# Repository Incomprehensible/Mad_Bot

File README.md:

# Mad_Bot
Exploratory project in Embedded Robotics and Swarm Algorithms

Warning: This is an ongoing project, and the repository is under construction!

## Features
* Small PCB-based frame, minimum 3D printed parts
* ESP32-S3 MCU with vector instructions, acceleration for neural network computing and signal processing workloads
* Wi-Fi, Bluetooth 5 and BLE connectivity
* Omnidirectional movement
* Quadrature encoders for precise movement
* 8 MB PSRAM for image processing
* 2 Megapixel camera and ToF sensors for running embedded robotics algorithms
* Powered via USB-C or 3000mAh LiPo battery with inner protection and external charging circuit
* Load sharing circuit for operating the robot while charging
* Buck-Boost converter for powering the MCU and peripherals
* 6V regulator for powering the middle power range motors
* ESPNOW, ESP-WIFI-MESH or ESP-BLE-MESH for communication between several robots
* Integrated MEMS microphone for sound recognition
* micro-ROS support

**Note**: Software support for some features is still in progress.

## Fusion360 design
| | |
|--------------|------------|
|  |  |
|  |  |

## URDF model
<details>

| Robot | Wheel |
|--------------|------------|
|  |  |

</details>

## Operation demo
<details>

| Forward movement | Backward movement | Rotation |
|:----------------:|:-----------------:|:--------:|
|  |  |  |
<!-- |  |  |  | -->

</details>

### Charging mode
<details>

</details>

## Board layout
<details>

</details>

## Future work
- [ ] Add a BOM
- [X] Design a carrier extension in Fusion360
- [X] Test battery charging circuit
- [X] Test load sharing circuit
- [X] Test basic functionality with motors and ESP32-S3
- [X] Test Wi-Fi
- [X] Motors library (in progress)
- [X] Encoders testing
- [ ] **Device firmware (in progress)**
- [ ] **Sensors testing (in progress)**:
  - [ ] Camera
  - [X] ToF
  - [X] IMU
  - [ ] *MEMS microphone (requires PCB bug fix)*
- [ ] Remote controller based on ESP32
- [ ] PSRAM memory testing
- [X] **ROS2 integration via micro-ROS (in progress)**
- [ ] Web page with control interface and telemetry
- [X] URDF model
- [X] Joystick control via ROS2
- [ ] Digital twin for simulation in Gazebo and Mujoco
- [ ] ESPNOW and Mesh experiments
- [ ] Multi-agent algorithms
- [ ] Computer vision algorithms
- [ ] Mini SLAM experiments

## Fix list for new hardware revisions
* MEMS microphone footprint flipped
* Non-fixed Buck-Boost mentioned in the schematics instead of 3.3V fixed
* 6V regulator doesn't disconnect the load if disabled because of topology - extra switch needed
* Battery connector is hard to remove - source power switch needed
* Better (aligned) placement for camera & ToF sensors

## Software Troubleshooting

### micro-ROS build issues
If you encounter issue like [this](https://github.com/micro-ROS/micro_ros_espidf_component/issues/251) building micro-ROS for the ESP32-S3 platform, edit [`libmicroros.mk`](https://github.com/micro-ROS/micro_ros_espidf_component/blob/humble/libmicroros.mk) file at line 110 to include `esp32s3` as follows:

```makefile
ifeq ($(IDF_TARGET),$(filter $(IDF_TARGET),esp32s2 esp32c3 esp32c6 esp32s3))
```

## Acknowledgements
This project takes inspiration from the following open-source projects:
* https://github.com/YePeOn7/ros2_omni_robot_sim (omnidirectional drive kinematics)
* https://github.com/twistx77/V53L7CX-Library.git (ToF sensor library)
* https://github.com/natanaeljr/esp32-mpu-driver (IMU driver)
* Jonas Scharpf code pf the PCA9685 driver (motor PWM driver)

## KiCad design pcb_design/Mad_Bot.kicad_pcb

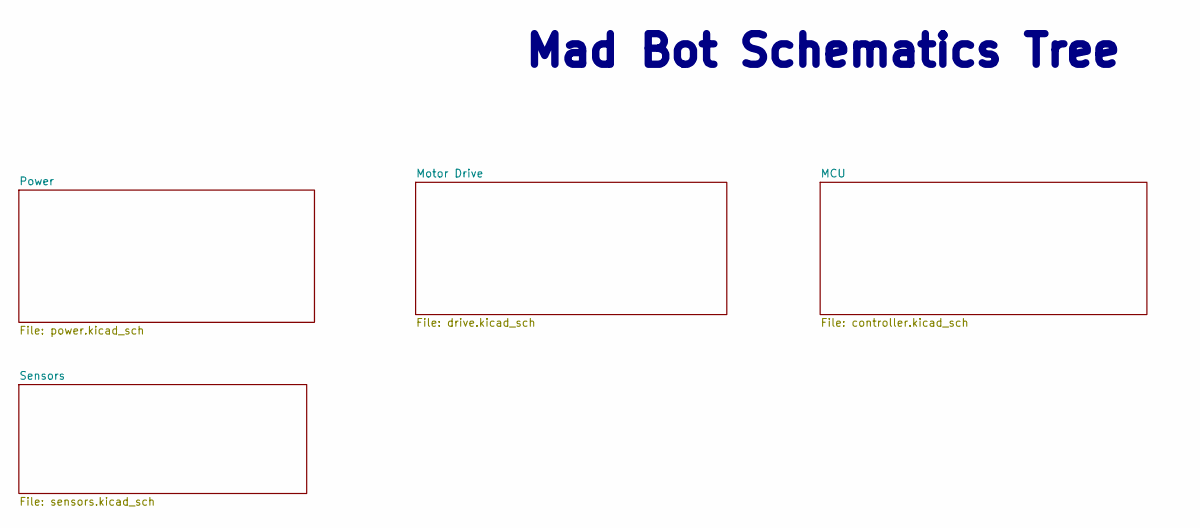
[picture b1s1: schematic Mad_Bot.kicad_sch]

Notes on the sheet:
Mad Bot Schematics Tree

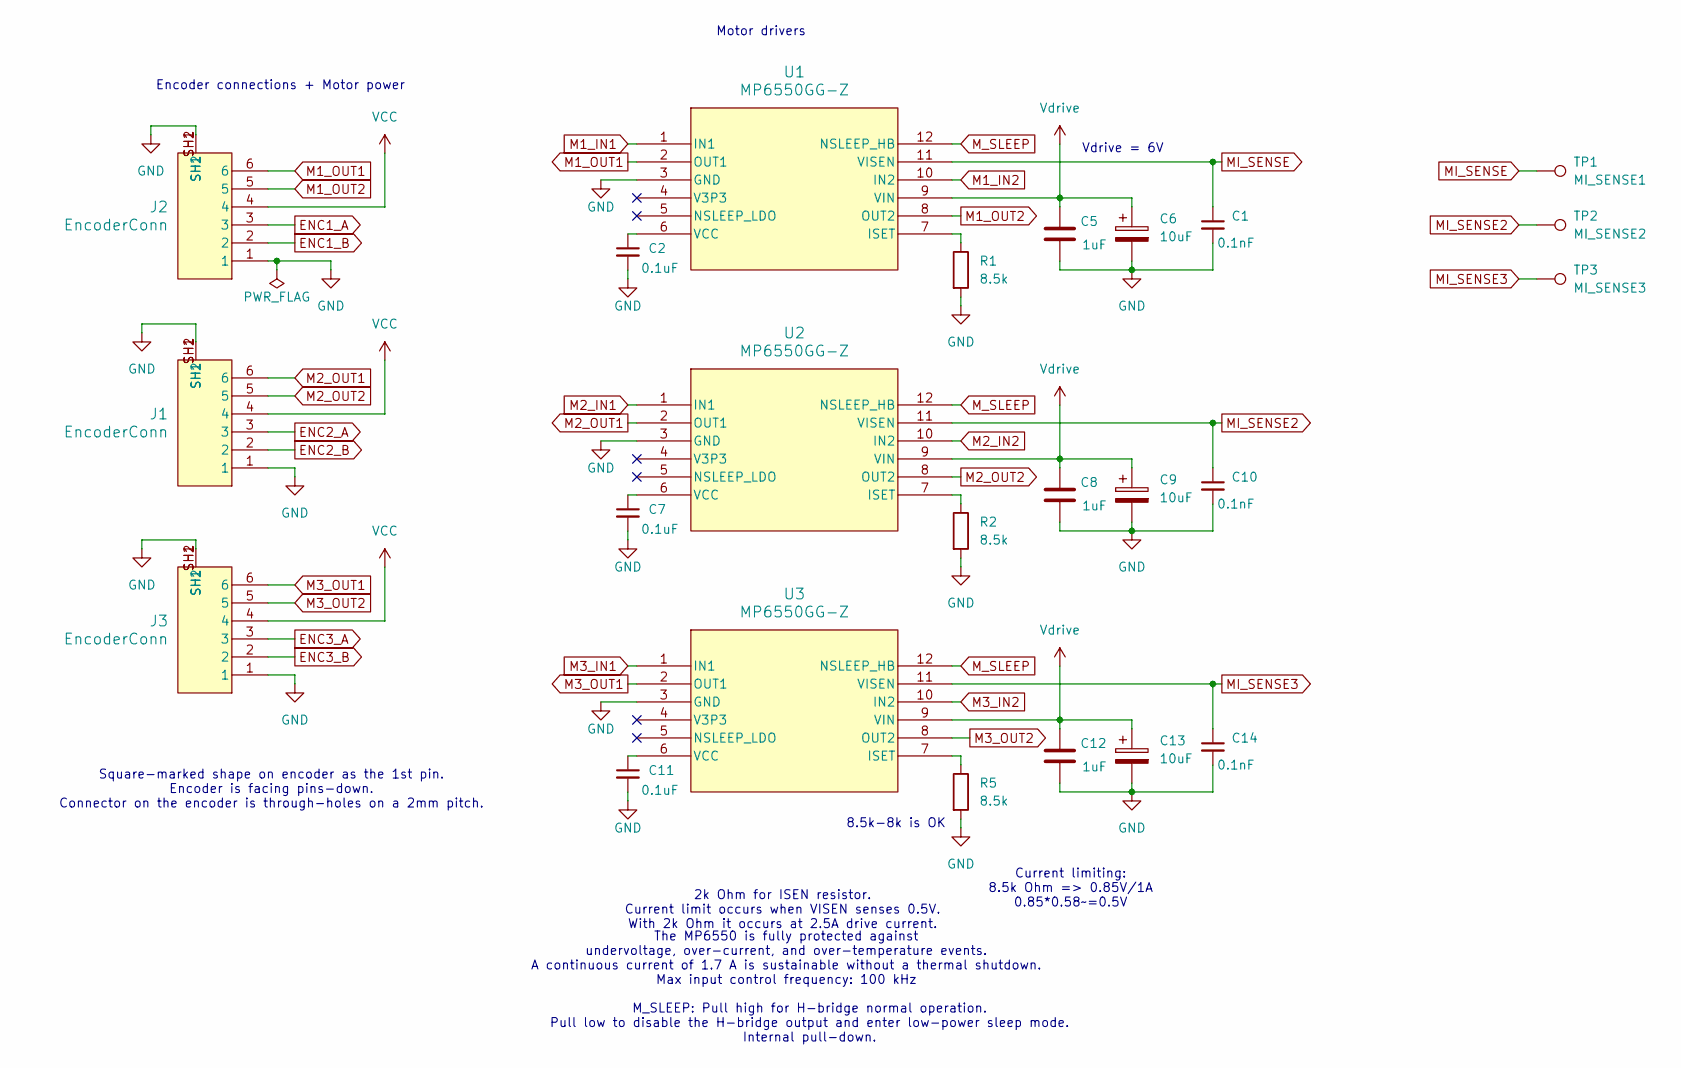
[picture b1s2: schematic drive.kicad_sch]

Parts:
C1, C10, C14: 0.1nF; C_0402_1005Metric_Pad0.74x0.62mm_HandSolder
C2, C7, C11: 0.1uF; C_0603_1608Metric_Pad1.08x0.95mm_HandSolder
C5, C8, C12: 1uF; CP_EIA-3216-18_Kemet-A_Pad1.58x1.35mm_HandSolder
C6, C9, C13: 10uF; C_1206_3216Metric_Pad1.33x1.80mm_HandSolder
J1, J2, J3: EncoderConn; JST_S6B-ZR-SM4A-TF_1.5mm
R1, R2, R5: 8.5k; R_0603_1608Metric_Pad0.98x0.95mm_HandSolder
TP1: MI_SENSE1; TestPoint_Pad_1.5x1.5mm
TP2: MI_SENSE2; TestPoint_Pad_1.5x1.5mm
TP3: MI_SENSE3; TestPoint_Pad_1.5x1.5mm
U1, U2, U3: MP6550GG-Z; IC12_MP6550_MNP

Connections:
ENC1_A: J2.3; also elsewhere on the board
ENC1_B: J2.2; also elsewhere on the board
ENC2_A: J1.3; also elsewhere on the board
ENC2_B: J1.2; also elsewhere on the board
ENC3_A: J3.3; also elsewhere on the board
ENC3_B: J3.2; also elsewhere on the board
GND: C1.2, C2.2, C5.2, C6.2, C7.2, C8.2, C9.2, C10.2, C11.2, C12.2, C13.2, C14.2, J1.1, J1.SH1, J1.SH2, J2.1, J2.SH1, J2.SH2, J3.1, J3.SH1, J3.SH2, R1.2, R2.2, R5.2, U1.3 (GND), U2.3 (GND), U3.3 (GND); also elsewhere on the board
M1_IN1: U1.1 (IN1); also elsewhere on the board
M1_IN2: U1.10 (IN2); also elsewhere on the board
M1_OUT1: J2.6, U1.2 (OUT1)
M1_OUT2: J2.5, U1.8 (OUT2)
M2_IN1: U2.1 (IN1); also elsewhere on the board
M2_IN2: U2.10 (IN2); also elsewhere on the board
M2_OUT1: J1.6, U2.2 (OUT1)
M2_OUT2: J1.5, U2.8 (OUT2)
M3_IN1: U3.1 (IN1); also elsewhere on the board
M3_IN2: U3.10 (IN2); also elsewhere on the board
M3_OUT1: J3.6, U3.2 (OUT1)
M3_OUT2: J3.5, U3.8 (OUT2)
MI_SENSE: C1.1, TP1.1, U1.11 (VISEN)
MI_SENSE2: C10.1, TP2.1, U2.11 (VISEN)
MI_SENSE3: C14.1, TP3.1, U3.11 (VISEN)
M_SLEEP: U1.12 (NSLEEP_HB), U2.12 (NSLEEP_HB), U3.12 (NSLEEP_HB); also elsewhere on the board
unnamed: R1.1, U1.7 (ISET)
unnamed: C2.1, U1.6 (VCC)
unnamed: R2.1, U2.7 (ISET)
unnamed: C7.1, U2.6 (VCC)
unnamed: R5.1, U3.7 (ISET)
unnamed: C11.1, U3.6 (VCC)
VCC: J1.4, J2.4, J3.4; also elsewhere on the board
Vdrive: C5.1, C6.1, C8.1, C9.1, C12.1, C13.1, U1.9 (VIN), U2.9 (VIN), U3.9 (VIN); also elsewhere on the board

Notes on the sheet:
M_SLEEP: Pull high for H-bridge normal operation. Pull low to disable the H-bridge output and enter low-power sleep mode. Internal pull-down.
Square-marked shape on encoder as the 1st pin. Encoder is facing pins-down. Connector on the encoder is through-holes on a 2mm pitch.
Motor drivers
8.5k-8k is OK
Current limiting: 8.5k Ohm => 0.85V/1A 0.85*0.58~=0.5V
Vdrive = 6V
Encoder connections + Motor power
The MP6550 is fully protected against undervoltage, over-current, and over-temperature events. A continuous current of 1.7 A is sustainable without a thermal shutdown. Max input control frequency: 100 kHz
2k Ohm for ISEN resistor. Current limit occurs when VISEN senses 0.5V. With 2k Ohm it occurs at 2.5A drive current.

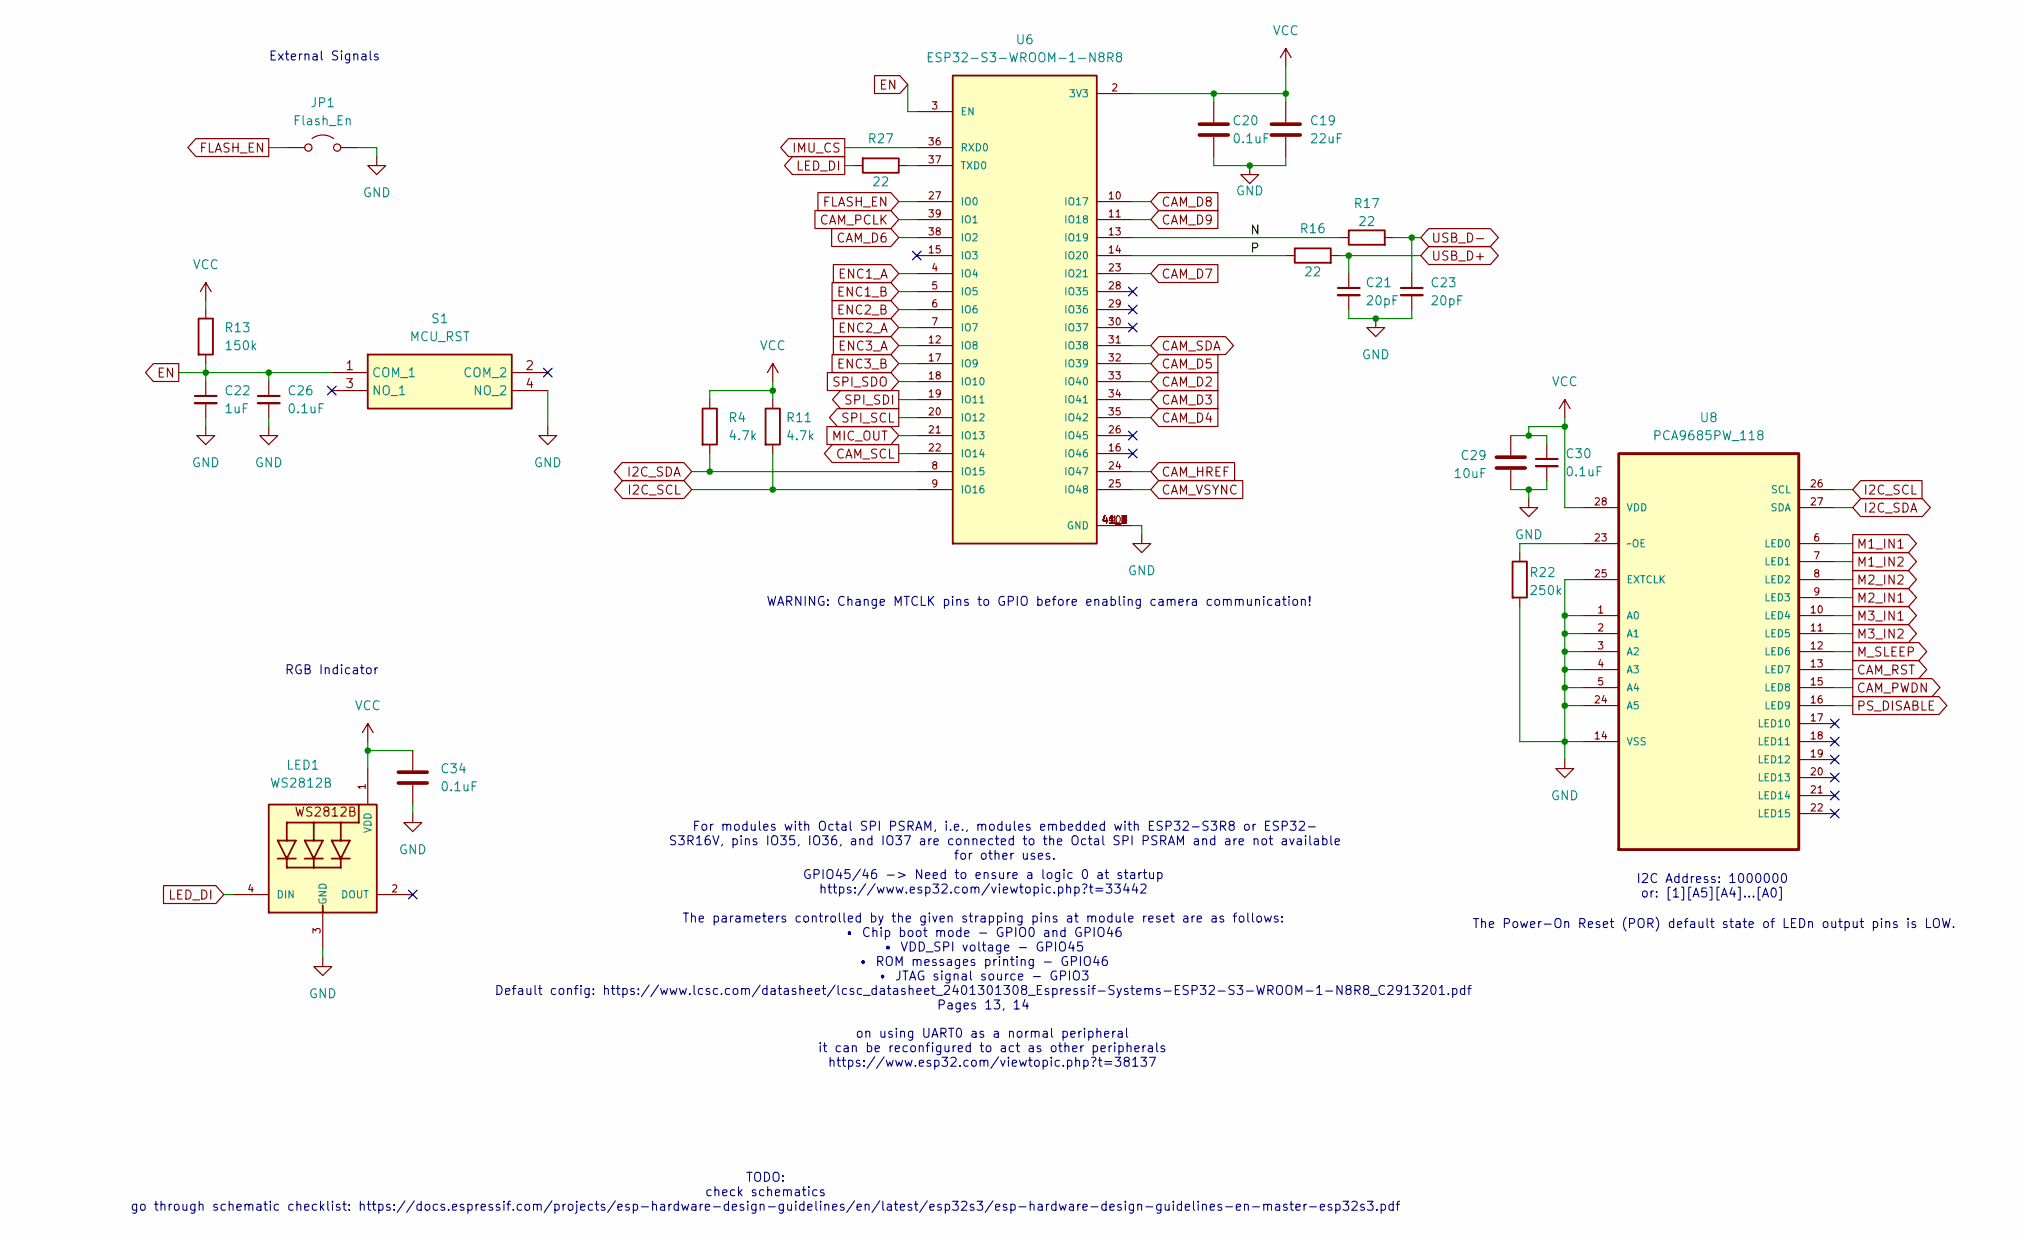
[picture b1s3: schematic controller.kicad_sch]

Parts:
C19: 22uF; C_0603_1608Metric_Pad1.08x0.95mm_HandSolder
C20, C26, C30, C34: 0.1uF; C_0603_1608Metric_Pad1.08x0.95mm_HandSolder
C21, C23: 20pF; C_0402_1005Metric_Pad0.74x0.62mm_HandSolder
C22: 1uF; CP_EIA-3216-18_Kemet-A_Pad1.58x1.35mm_HandSolder
C29: 10uF; C_1206_3216Metric_Pad1.33x1.80mm_HandSolder
JP1: Flash_En; Flash_Jumper_1x02_P2.00mm_Vertical
LED1: WS2812B
R4, R11: 4.7k; R_0603_1608Metric_Pad0.98x0.95mm_HandSolder
R13: 150k; R_0603_1608Metric_Pad0.98x0.95mm_HandSolder
R16, R17: 22; R_0402_1005Metric_Pad0.72x0.64mm_HandSolder
R22: 250k; R_0603_1608Metric_Pad0.98x0.95mm_HandSolder
R27: 22; R_0603_1608Metric_Pad0.98x0.95mm_HandSolder
S1: MCU_RST; PTS526SK15SMTR2LFS; Manufacturer_Part_Number PTS526 SK15 SMTR2 LFS; Mouser Part Number 611-PTS526SK15SMR2L
U6: ESP32-S3-WROOM-1-N8R8; XCVR_ESP32S3WROOM1N8R8
U8: PCA9685PW_118; SOP65P640X110-28N; MPN PCA9685PW,118

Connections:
/MCU/N: R17.1, U6.13 (IO19)
/MCU/P: R16.1, U6.14 (IO20)
CAM_D2: U6.33 (IO40); also elsewhere on the board
CAM_D3: U6.34 (IO41); also elsewhere on the board
CAM_D4: U6.35 (IO42); also elsewhere on the board
CAM_D5: U6.32 (IO39); also elsewhere on the board
CAM_D6: U6.38 (IO2); also elsewhere on the board
CAM_D7: U6.23 (IO21); also elsewhere on the board
CAM_D8: U6.10 (IO17); also elsewhere on the board
CAM_D9: U6.11 (IO18); also elsewhere on the board
CAM_HREF: U6.24 (IO47); also elsewhere on the board
CAM_PCLK: U6.39 (IO1); also elsewhere on the board
CAM_PWDN: U8.15 (LED8); also elsewhere on the board
CAM_RST: U8.13 (LED7); also elsewhere on the board
CAM_SCL: U6.22 (IO14); also elsewhere on the board
CAM_SDA: U6.31 (IO38); also elsewhere on the board
CAM_VSYNC: U6.25 (IO48); also elsewhere on the board
EN: C22.1, C26.1, R13.2, S1.1 (COM_1), U6.3 (EN)
ENC1_A: U6.4 (IO4); also elsewhere on the board
ENC1_B: U6.5 (IO5); also elsewhere on the board
ENC2_A: U6.7 (IO7); also elsewhere on the board
ENC2_B: U6.6 (IO6); also elsewhere on the board
ENC3_A: U6.12 (IO8); also elsewhere on the board
ENC3_B: U6.17 (IO9); also elsewhere on the board
FLASH_EN: JP1.1 (A), U6.27 (IO0)
GND: C19.2, C20.2, C21.2, C22.2, C23.2, C26.2, C29.1, C30.2, C34.2, JP1.2 (B), LED1.3 (GND), R22.2, S1.4 (NO_2), U6.1 (GND), U6.40 (GND), U6.41_1 (GND), U6.41_2 (GND), U6.41_3 (GND), U6.41_4 (GND), U6.41_5 (GND), U6.41_6 (GND), U6.41_7 (GND), U6.41_8 (GND), U6.41_9 (GND), U8.1 (A0), U8.2 (A1), U8.3 (A2), U8.4 (A3), U8.5 (A4), U8.14 (VSS), U8.24 (A5), U8.25 (EXTCLK); also elsewhere on the board
I2C_SCL: R11.2, U6.9 (IO16), U8.26 (SCL); also elsewhere on the board
I2C_SDA: R4.2, U6.8 (IO15), U8.27 (SDA); also elsewhere on the board
IMU_CS: U6.36 (RXD0); also elsewhere on the board
LED_DI: LED1.4 (DIN), R27.2
M1_IN1: U8.6 (LED0); also elsewhere on the board
M1_IN2: U8.7 (LED1); also elsewhere on the board
M2_IN1: U8.9 (LED3); also elsewhere on the board
M2_IN2: U8.8 (LED2); also elsewhere on the board
M3_IN1: U8.10 (LED4); also elsewhere on the board
M3_IN2: U8.11 (LED5); also elsewhere on the board
MIC_OUT: U6.21 (IO13); also elsewhere on the board
M_SLEEP: U8.12 (LED6); also elsewhere on the board
unnamed: R27.1, U6.37 (TXD0)
unnamed: R22.1, U8.23 (~OE)
PS_DISABLE: U8.16 (LED9); also elsewhere on the board
SPI_SCL: U6.20 (IO12); also elsewhere on the board
SPI_SDI: U6.19 (IO11); also elsewhere on the board
SPI_SDO: U6.18 (IO10); also elsewhere on the board
USB_D+: C21.1, R16.2; also elsewhere on the board
USB_D-: C23.1, R17.2; also elsewhere on the board
VCC: C19.1, C20.1, C29.2, C30.1, C34.1, LED1.1 (VDD), R4.1, R11.1, R13.1, U6.2 (3V3), U8.28 (VDD); also elsewhere on the board

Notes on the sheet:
GPIO45/46 -> Need to ensure a logic 0 at startup https://www.esp32.com/viewtopic.php?t=33442 The parameters controlled by the given strapping pins at module reset are as follows: • Chip boot mode - GPIO0 and GPIO46 • VDD_SPI voltage - GPIO45 • ROM messages printing - GPIO46 • JTAG signal source - G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
TODO: check schematics go through schematic checklist: https://docs.espressif.com/projects/esp-hardware-design-guidelines/en/latest/esp32s3/esp-hardware-design-guidelines-en-master-esp32s3.pdf
External Signals
I2C Address: 1000000 or: [1][A5][A4]...[A0]
on using UART0 as a normal peripheral it can be reconfigured to act as other peripherals https://www.esp32.com/viewtopic.php?t=38137
The Power-On Reset (POR) default state of LEDn output pins is LOW.
RGB Indicator
For modules with Octal SPI PSRAM, i.e., modules embedded with ESP32-S3R8 or ESP32- S3R16V, pins IO35, IO36, and IO37 are connected to the Octal SPI PSRAM and are not available for other uses.
WARNING: Change MTCLK pins to GPIO before enabling camera communication!

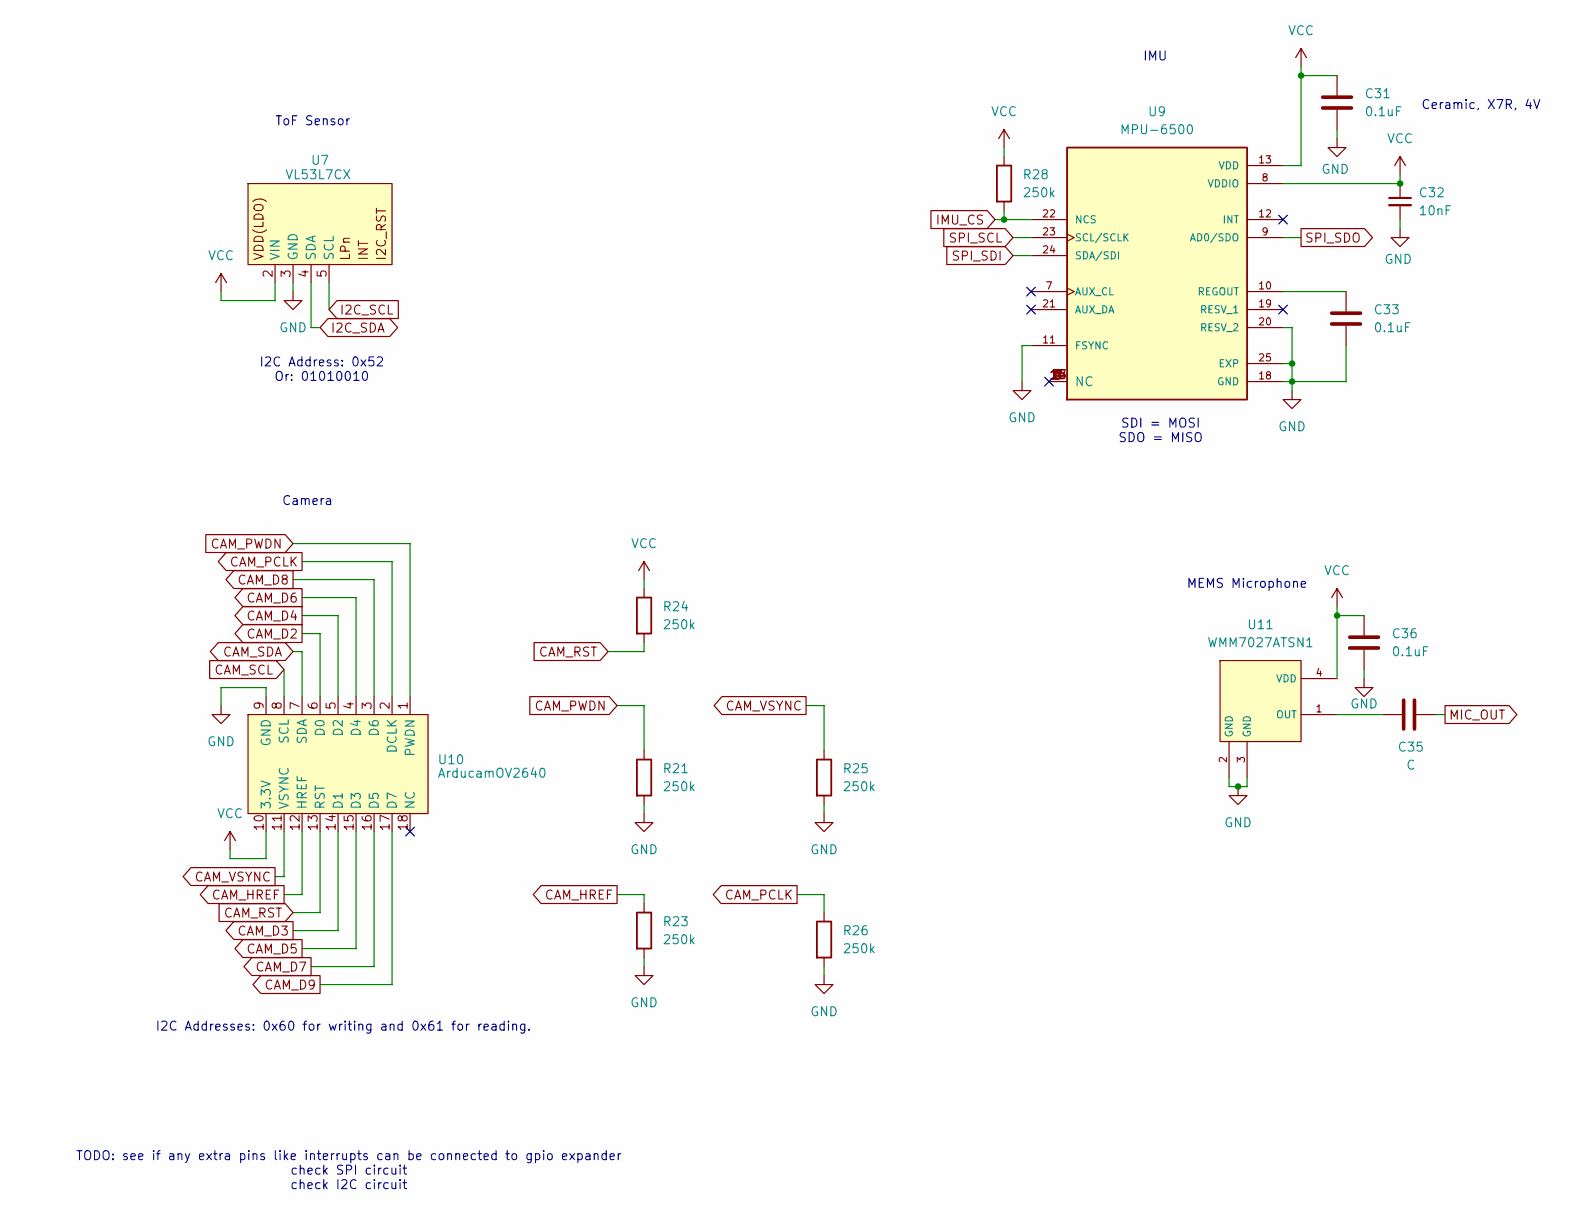
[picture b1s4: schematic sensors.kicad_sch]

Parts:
C31, C33, C36: 0.1uF; C_0603_1608Metric_Pad1.08x0.95mm_HandSolder
C32: 10nF; C_0603_1608Metric_Pad1.08x0.95mm_HandSolder
C35: C; C_0603_1608Metric_Pad1.08x0.95mm_HandSolder
R21, R23, R24, R25, R26, R28: 250k; R_0603_1608Metric_Pad0.98x0.95mm_HandSolder
U7: VL53L7CX; CONN_S4B-XH-SM4-TB_JST
U9: MPU-6500; QFN24_3X3X0P9_MPU6500; PARTREV 1.3
U10: ArducamOV2640; Arducam_Socket_2x09_P2.54mm_Vertical_SMD
U11: WMM7027ATSN1; WMM7027ATSN1-4TR

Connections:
CAM_D2: U10.6 (D0); also elsewhere on the board
CAM_D3: U10.14 (D1); also elsewhere on the board
CAM_D4: U10.5 (D2); also elsewhere on the board
CAM_D5: U10.15 (D3); also elsewhere on the board
CAM_D6: U10.4 (D4); also elsewhere on the board
CAM_D7: U10.16 (D5); also elsewhere on the board
CAM_D8: U10.3 (D6); also elsewhere on the board
CAM_D9: U10.17 (D7); also elsewhere on the board
CAM_HREF: R23.1, U10.12 (HREF); also elsewhere on the board
CAM_PCLK: R26.1, U10.2 (DCLK); also elsewhere on the board
CAM_PWDN: R21.1, U10.1 (PWDN); also elsewhere on the board
CAM_RST: R24.2, U10.13 (RST); also elsewhere on the board
CAM_SCL: U10.8 (SCL); also elsewhere on the board
CAM_SDA: U10.7 (SDA); also elsewhere on the board
CAM_VSYNC: R25.1, U10.11 (VSYNC); also elsewhere on the board
GND: C31.2, C32.2, C33.2, C36.2, R21.2, R23.2, R25.2, R26.2, U7.3 (GND), U9.11 (FSYNC), U9.18 (GND), U9.20 (RESV_2), U9.25 (EXP), U10.9 (GND), U11.2 (GND), U11.3 (GND); also elsewhere on the board
I2C_SCL: U7.5 (SCL); also elsewhere on the board
I2C_SDA: U7.4 (SDA); also elsewhere on the board
IMU_CS: R28.2, U9.22 (NCS); also elsewhere on the board
MIC_OUT: C35.2; also elsewhere on the board
unnamed: C33.1, U9.10 (REGOUT)
unnamed: C35.1, U11.1 (OUT)
SPI_SCL: U9.23 (SCL/SCLK); also elsewhere on the board
SPI_SDI: U9.24 (SDA/SDI); also elsewhere on the board
SPI_SDO: U9.9 (AD0/SDO); also elsewhere on the board
VCC: C31.1, C32.1, C36.1, R24.1, R28.1, U7.2 (VIN), U9.8 (VDDIO), U9.13 (VDD), U10.10 (3.3V), U11.4 (VDD); also elsewhere on the board

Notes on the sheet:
SDI = MOSI SDO = MISO
Camera
I2C Addresses: 0x60 for writing and 0x61 for reading.
TODO: see if any extra pins like interrupts can be connected to gpio expander check SPI circuit check I2C circuit
Ceramic, X7R, 4V
ToF Sensor
I2C Address: 0x52 Or: 01010010
IMU
MEMS Microphone

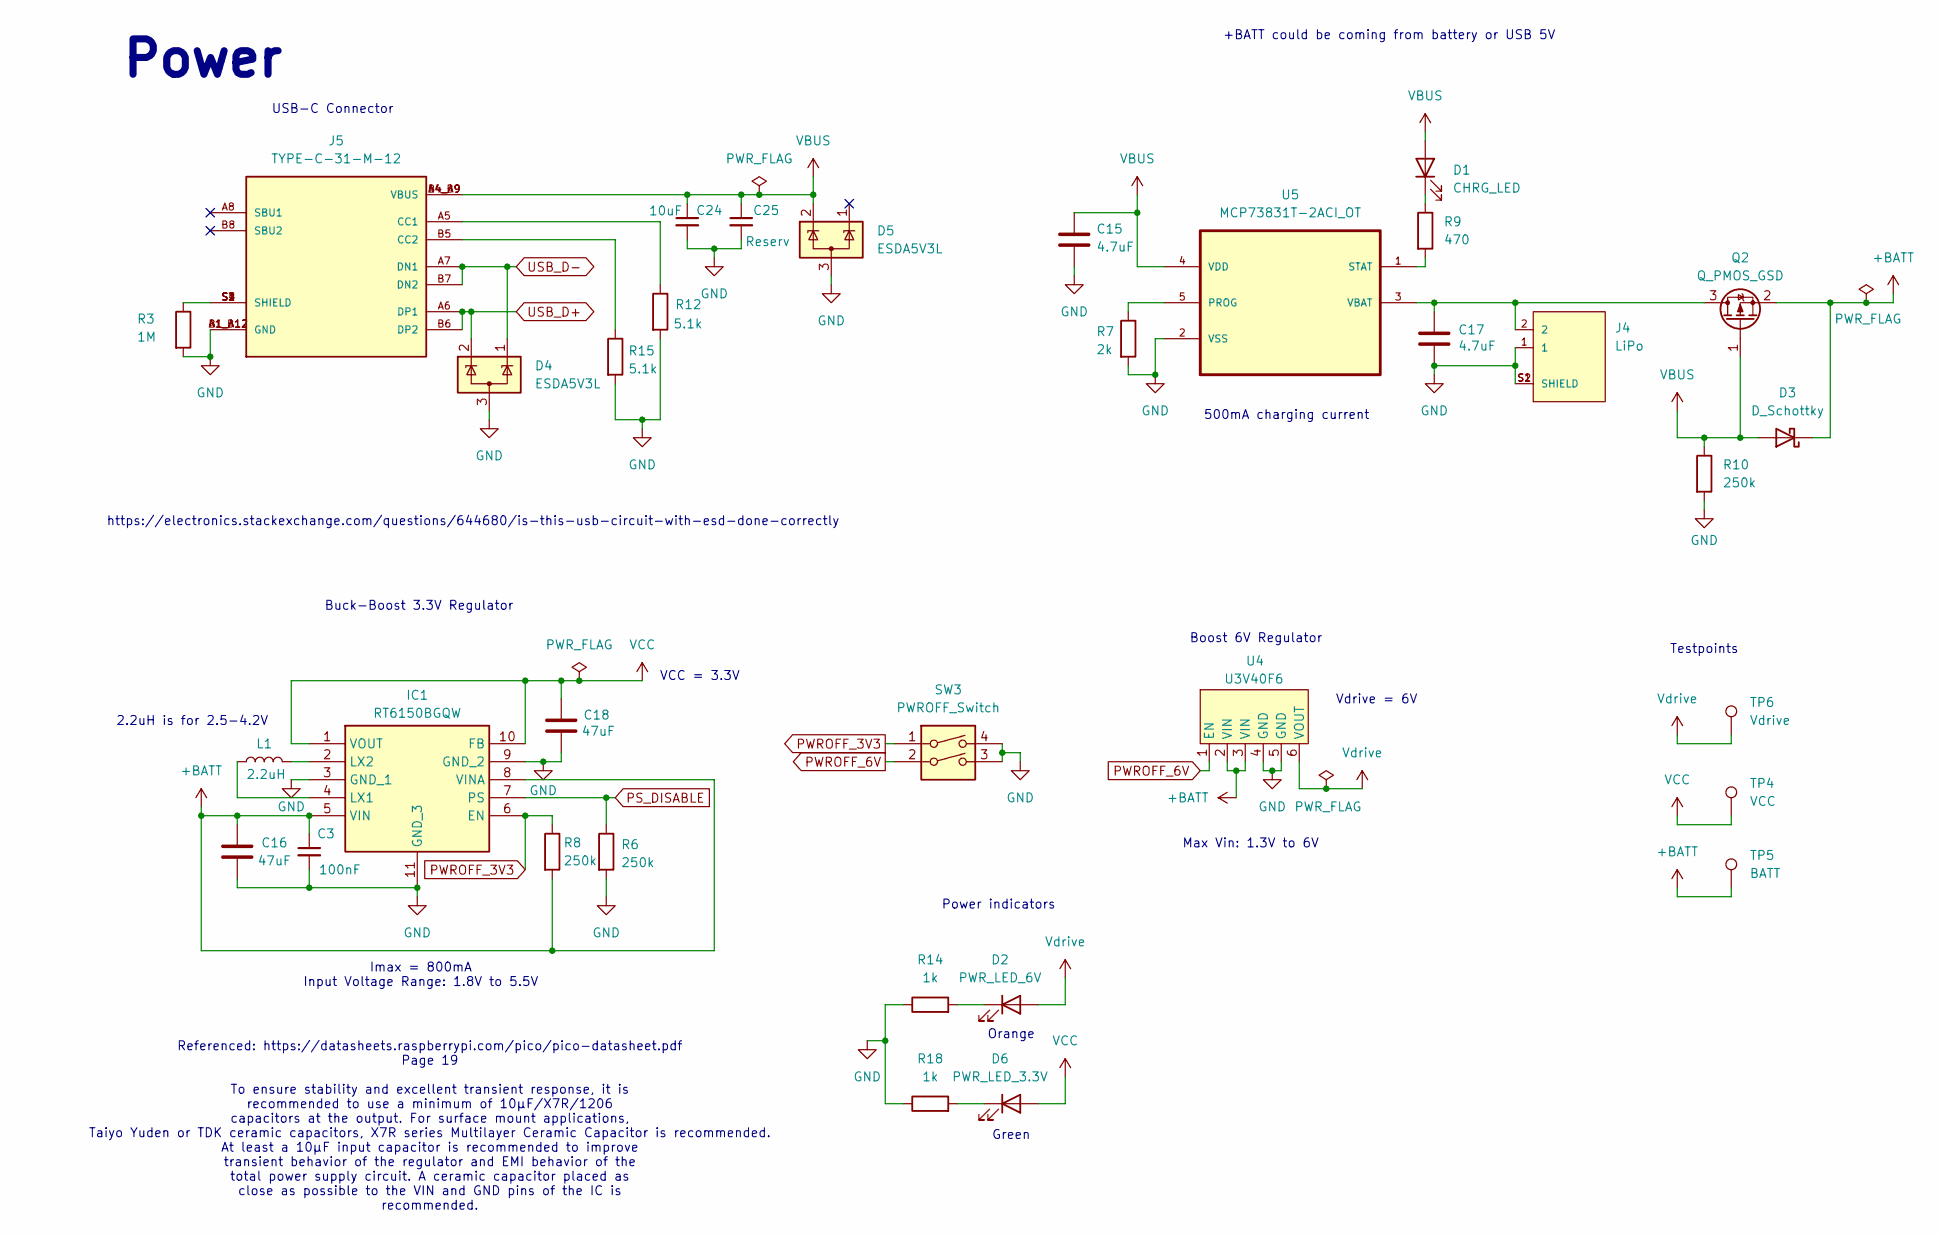
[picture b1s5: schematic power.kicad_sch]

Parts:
C3: 100nF; C_0603_1608Metric_Pad1.08x0.95mm_HandSolder
C15, C17: 4.7uF; C_0603_1608Metric_Pad1.08x0.95mm_HandSolder
C16, C18: 47uF; C_1210_3225Metric_Pad1.33x2.70mm_HandSolder
C24: 10uF; C_1206_3216Metric_Pad1.33x1.80mm_HandSolder
C25: Reserv; C_0603_1608Metric_Pad1.08x0.95mm_HandSolder
D1: CHRG_LED; LED_0603_1608Metric_Pad1.05x0.95mm_HandSolder
D2: PWR_LED_6V; LED_0805_2012Metric_Pad1.15x1.40mm_HandSolder
D3: D_Schottky; D_SOD-123F
D4, D5: ESDA5V3L; SOT-23
D6: PWR_LED_3.3V; LED_0805_2012Metric_Pad1.15x1.40mm_HandSolder
IC1: RT6150BGQW; SON50P250X250X80-11N-D; Mouser Part Number 835-RT6150BGQW
J4: LiPo; JST_S2B-PH-SM4-TB_LF__SN_
J5: TYPE-C-31-M-12; HRO_TYPE-C-31-M-12; PARTREV 2020.12.08
L1: 2.2uH; FNR4020S2R2MT
Q2: Q_PMOS_GSD; SOT-23
R3: 1M; R_0603_1608Metric_Pad0.98x0.95mm_HandSolder
R6, R8, R10: 250k; R_0603_1608Metric_Pad0.98x0.95mm_HandSolder
R7: 2k; R_0603_1608Metric_Pad0.98x0.95mm_HandSolder
R9: 470; R_0603_1608Metric_Pad0.98x0.95mm_HandSolder
R12, R15: 5.1k; R_0603_1608Metric_Pad0.98x0.95mm_HandSolder
R14, R18: 1k; R_0603_1608Metric_Pad0.98x0.95mm_HandSolder
SW3: PWROFF_Switch; DV7SA-02F-01_SW_DIP_SPSTx02_Slide
TP4: VCC; TestPoint_Pad_1.5x1.5mm
TP5: BATT; TestPoint_Pad_1.5x1.5mm
TP6: Vdrive; TestPoint_Pad_1.5x1.5mm
U4: U3V40F6; U3V40F6_upd
U5: MCP73831T-2ACI_OT; SOT95P280X145-5N; MPN MCP73831T-2ACI/OT

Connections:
+BATT: C3.1, C16.1, D3.1 (K), IC1.5 (VIN), IC1.8 (VINA), Q2.2 (S), R8.2, TP5.1, U4.2 (VIN), U4.3 (VIN)
GND: C3.2, C15.2, C16.2, C17.2, C18.2, C24.2, C25.2, D4.3 (A), D5.3 (A), IC1.3 (GND_1), IC1.9 (GND_2), IC1.11 (GND_3), J4.1, J4.S1 (SHIELD), J4.S2 (SHIELD), J5.A1_B12 (GND), J5.B1_A12 (GND), R3.2, R6.2, R7.2, R10.2, R12.2, R14.1, R15.2, R18.1, SW3.3, SW3.4, U4.4 (GND), U4.5 (GND), U5.2 (VSS); also elsewhere on the board
unnamed: D1.1 (K), R9.1
unnamed: D2.1 (K), R14.2
unnamed: D6.1 (K), R18.2
unnamed: IC1.4 (LX1), L1.1
unnamed: IC1.2 (LX2), L1.2
unnamed: J5.A5 (CC1), R12.1
unnamed: J5.B5 (CC2), R15.1
unnamed: J5.S1 (SHIELD), J5.S2 (SHIELD), J5.S3 (SHIELD), J5.S4 (SHIELD), R3.1
unnamed: C17.1, J4.2, Q2.3 (D), U5.3 (VBAT)
unnamed: R7.1, U5.5 (PROG)
unnamed: R9.2, U5.1 (STAT)
PS_DISABLE: IC1.7 (PS), R6.1; also elsewhere on the board
PWROFF_3V3: IC1.6 (EN), R8.1, SW3.1
PWROFF_6V: SW3.2, U4.1 (EN)
USB_D+: D4.2 (K), J5.A6 (DP1), J5.B6 (DP2); also elsewhere on the board
USB_D-: D4.1 (K), J5.A7 (DN1), J5.B7 (DN2); also elsewhere on the board
VBUS: C15.1, C24.1, C25.1, D1.2 (A), D3.2 (A), D5.2 (K), J5.A4_B9 (VBUS), J5.B4_A9 (VBUS), Q2.1 (G), R10.1, U5.4 (VDD)
VCC: C18.1, D6.2 (A), IC1.1 (VOUT), IC1.10 (FB), TP4.1; also elsewhere on the board
Vdrive: D2.2 (A), TP6.1, U4.6 (VOUT); also elsewhere on the board

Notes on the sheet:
Referenced: https://datasheets.raspberrypi.com/pico/pico-datasheet.pdf Page 19 To ensure stability and excellent transient response, it is recommended to use a minimum of 10μF/X7R/1206 capacitors at the output. For surface mount applications, Taiyo Yuden or TDK ceramic capacitors, X7R series Multil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
Boost 6V Regulator
Testpoints
Vdrive = 6V
Green
Max Vin: 1.3V to 6V
2.2uH is for 2.5-4.2V
500mA charging current
Buck-Boost 3.3V Regulator
Power indicators
Power
https://electronics.stackexchange.com/questions/644680/is-this-usb-circuit-with-esd-done-correctly
+BATT could be coming from battery or USB 5V
VCC = 3.3V
USB-C Connector
Orange
Imax = 800mA Input Voltage Range: 1.8V to 5.5V

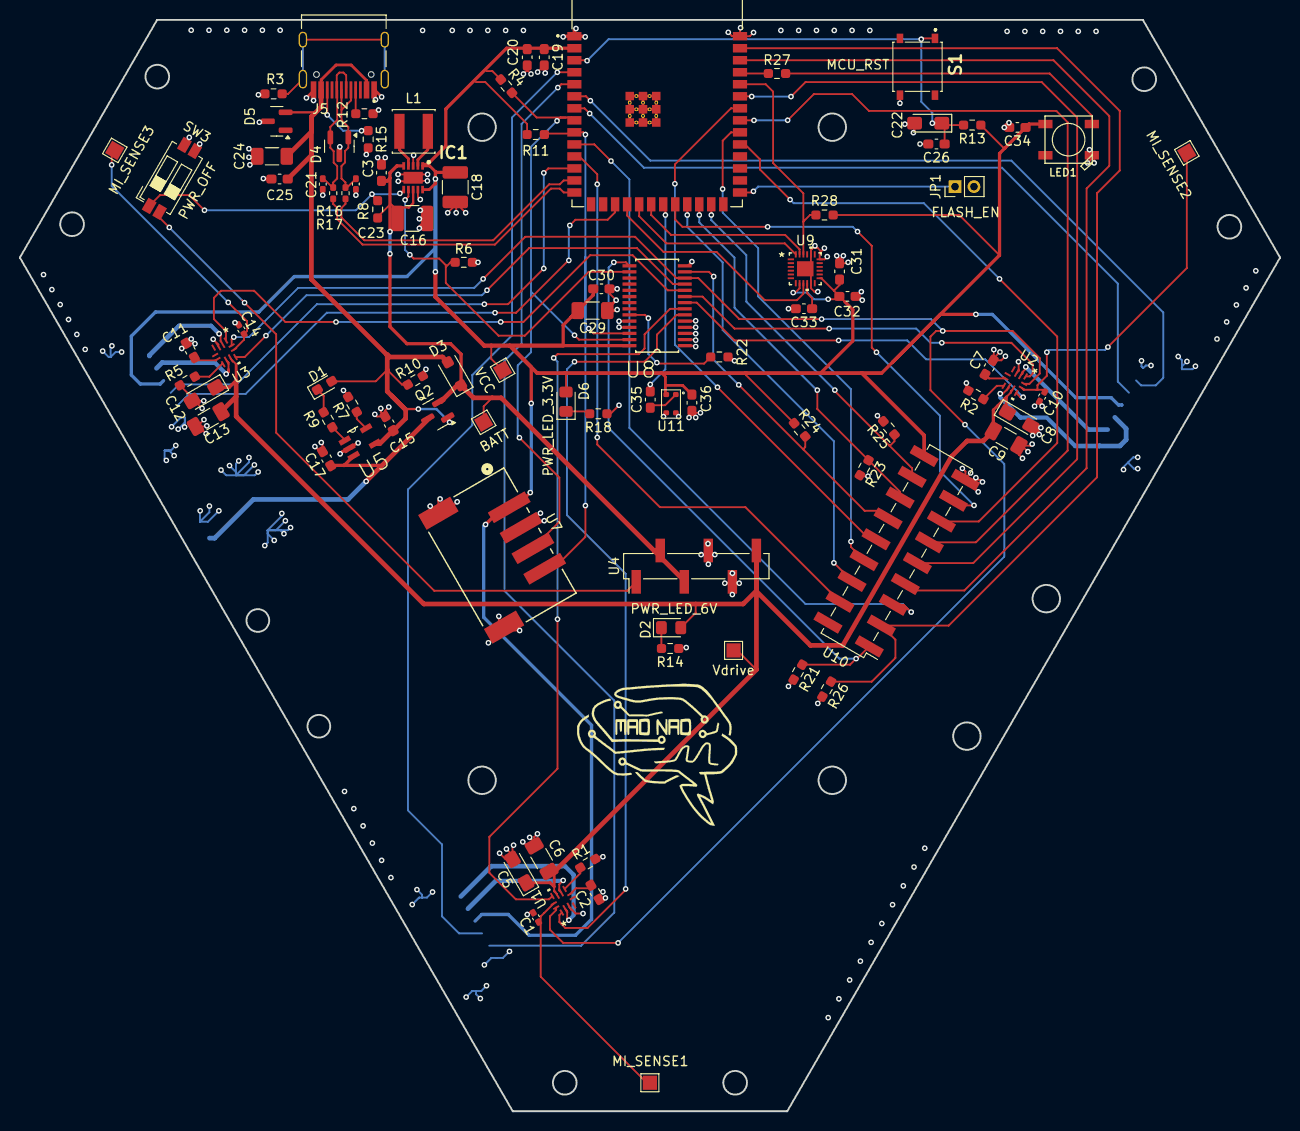
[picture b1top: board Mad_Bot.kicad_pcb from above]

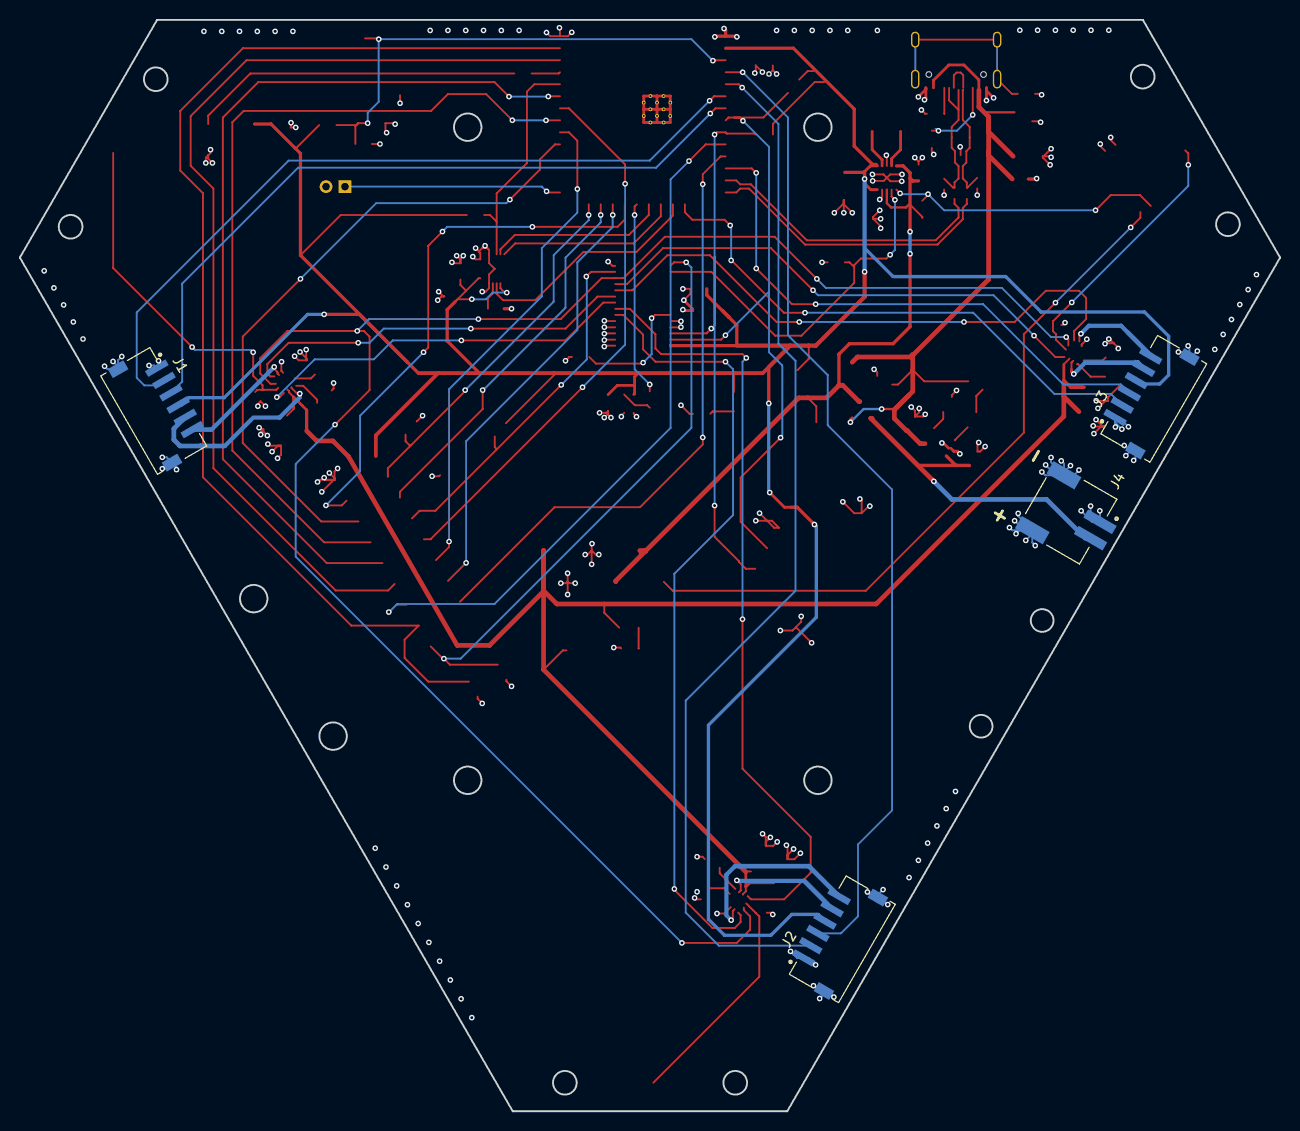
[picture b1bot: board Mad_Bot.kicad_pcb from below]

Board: 4 copper layers, 133.1 x 115.3 mm, 94 parts (4 on the bottom side), 80 nets.

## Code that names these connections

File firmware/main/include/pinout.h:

#ifndef PINOUT_H
#define PINOUT_H

#define M1_IN1 0
#define M1_IN2 1
#define M2_IN1 3
#define M2_IN2 2
#define M3_IN1 4
#define M3_IN2 5
#define M_SLEEP 6

#define SPI_MOSI 11
#define SPI_MISO 10
#define SPI_CLK 12
#define SPI_CS 44 // RXD0(GPIO44)

#define ENC_A1 4
#define ENC_B1 5

#define ENC_A2 7
#define ENC_B2 6

#define ENC_A3 8
#define ENC_B3 9


#endif

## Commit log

2024-09-17 Uploaded the raw Ver0 of the project: CAD and KiCad files.
2024-09-18 Fixed silkscreen, modified PCB design, complied with DRC.
2024-09-18 Updated gallery. Uploaded fusion project.
2024-09-19 Fixed mistake in battery bypass circuit.
2024-09-20 Added Gerber files belonging to the release.
2024-09-20 Rerouted part of the board containing 3.3v regulator and USB connectivity. Routed 90ohm diff pair controlled-impedance traces for USB 2.0 Full Speed.
2024-10-14 Updated hardware issues found after first-stage assembly.
2025-04-12 Updated README with features and TODO.
2025-04-12 Updated README with operation demo.
2025-04-12 Updated README.
2025-04-14 Updated README due to testing progress.
2025-04-14 Updated README due to dev progress.
2025-04-18 Added command demo and micro-ROS firmware example.
2025-04-18 Removed old readme
2025-11-02 Updated software dependencies. Added raw motor control code.
2025-11-27 feat: Added updated fusion design, software joystick code, URDF model. Updated README.
2025-12-08 fix: Submodule fix.
